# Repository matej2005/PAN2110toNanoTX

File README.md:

# PAN2110toNanoTX
PAN2110 TX module for Radiomaster Pocket external bay

[documentation](https://docs.panchip.com/pan211xdk-doc/index.html)

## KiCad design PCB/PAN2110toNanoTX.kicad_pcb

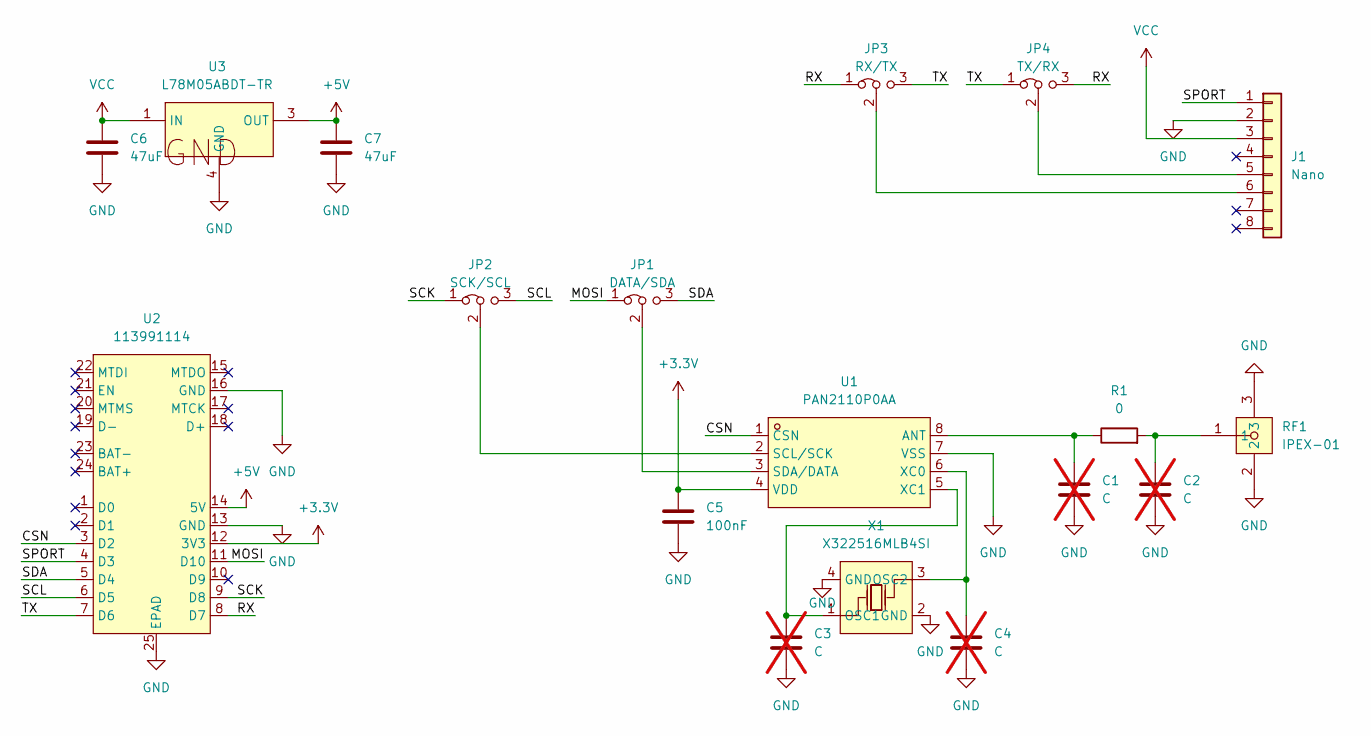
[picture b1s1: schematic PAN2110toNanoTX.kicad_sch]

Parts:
C1, C2, C3, C4: C; C_0603_1608Metric_Pad1.08x0.95mm_HandSolder; not fitted
C5: 100nF; C_0603_1608Metric; JLCPCB Part # C14663
C6, C7: 47uF; C_0805_2012Metric; Voltage Rating 6.3V; JLCPCB Part # C16780
J1: Nano; PinHeader_1x08_P2.54mm_Horizontal
JP1: DATA/SDA; SolderJumper-3_P1.3mm_Bridged12_Pad1.0x1.5mm
JP2: SCK/SCL; SolderJumper-3_P1.3mm_Bridged12_Pad1.0x1.5mm
JP3: RX/TX; SolderJumper-3_P1.3mm_Bridged12_Pad1.0x1.5mm
JP4: TX/RX; SolderJumper-3_P1.3mm_Bridged12_Pad1.0x1.5mm
R1: 0; R_0603_1608Metric_Pad0.98x0.95mm_HandSolder; JLCPCB Part # C21189
RF1: IPEX-01; IPEX-SMD_3P-L2.6-W2.6-LS3.0_YUANDI_RF-001; MPN IPEX-01; LCSC Part C36936657
U1: PAN2110P0AA; SOIC-8_L5.0-W4.0-P1.27-LS6.0-BL; MPN PAN2110P0AA; LCSC Part C52268929
U2: 113991114; COMM-SMD_L21.1-W17.8-P2.54_113991114_XIAO-ESP32-S3; MPN 113991114; LCSC Part C20467913
U3: L78M05ABDT-TR; TO-252-2_L6.5-W6.1-P4.58-LS10.0-TL; MPN L78M05ABDT-TR; LCSC Part C58069
X1: X322516MLB4SI; CRYSTAL-SMD_4P-L3.2-W2.5-BL; MPN X322516MLB4SI; LCSC Part C13738

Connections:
+3.3V: C5.1, U1.4 (VDD), U2.12 (3V3)
+5V: C7.1, U2.14 (5V), U3.3 (OUT)
/CSN: U1.1 (CSN), U2.3 (D2)
/MOSI: JP1.1 (A), U2.11 (D10)
/RX: JP3.1 (A), JP4.3 (B), U2.8 (D7)
/SCK: JP2.1 (A), U2.9 (D8)
/SCL: JP2.3 (B), U2.6 (D5)
/SDA: JP1.3 (B), U2.5 (D4)
/SPORT: J1.1, U2.4 (D3)
/TX: JP3.3 (B), JP4.1 (A), U2.7 (D6)
GND: C1.2, C2.2, C3.2, C4.2, C5.2, C6.2, C7.2, J1.2, RF1.2, RF1.3, U1.7 (VSS), U2.13 (GND), U2.16 (GND), U2.25 (EPAD), U3.4 (GND), X1.2 (GND), X1.4 (GND)
unnamed: C2.1, R1.2, RF1.1
unnamed: J1.5, JP4.2 (C)
unnamed: J1.6, JP3.2 (C)
unnamed: JP1.2 (C), U1.3 (SDA/DATA)
unnamed: JP2.2 (C), U1.2 (SCL/SCK)
unnamed: C1.1, R1.1, U1.8 (ANT)
unnamed: C4.1, U1.6 (XC0), X1.3 (OSC2)
unnamed: C3.1, U1.5 (XC1), X1.1 (OSC1)
VCC: C6.1, J1.3, U3.1 (IN)

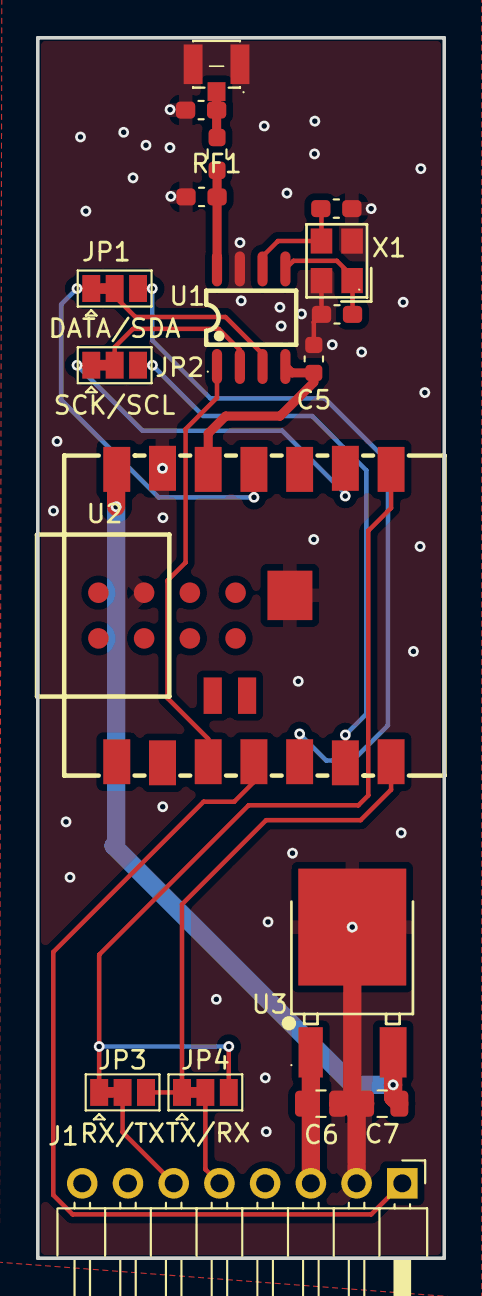
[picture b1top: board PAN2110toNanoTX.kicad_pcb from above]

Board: 2 copper layers, 22.6 x 67.8 mm, 18 parts (0 on the bottom side), 20 nets.
